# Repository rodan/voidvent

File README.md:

## voidvent

 ////// UNDER DEVELOPMENT ///////////////////////

 room climate control project that replaces the microcontroller inside a blueair pro air purifier with a transceiver-enabled cc430f5137 devboard from Olimex.

```
 source:       https://github.com/rodan/voidvent
 author:       Petre Rodan <2b4eda@subdimension.ro>
 license:      BSD
```

### Features

 * RF-based remote control of the air purifier via Intertechno ITLS-16
 * limit the ionizer activity to a custom number of minutes per hour (3 levels)
 * control air extractor via RF signal
 * control window opening via RF signal
 
### Components

project directory structure

 * ./firmware/base_station/ - source code for the base station
 * ./firmware/window_control/ - source code for the window opening jig
 * ./hardware/blueair_pro_m/ - kicad schematics of the digital subsystem of the air purifier

### Build requirements

you will need TI's excelent [GCC toolchain](https://www.ti.com/tool/MSP430-GCC-OPENSOURCE) or Code Composer Studio for linux and my [reference libraries for msp430 micros](https://github.com/rodan/atlas430) cloned in /opt/.

```
cd ./firmware/base_station
make
make install
```

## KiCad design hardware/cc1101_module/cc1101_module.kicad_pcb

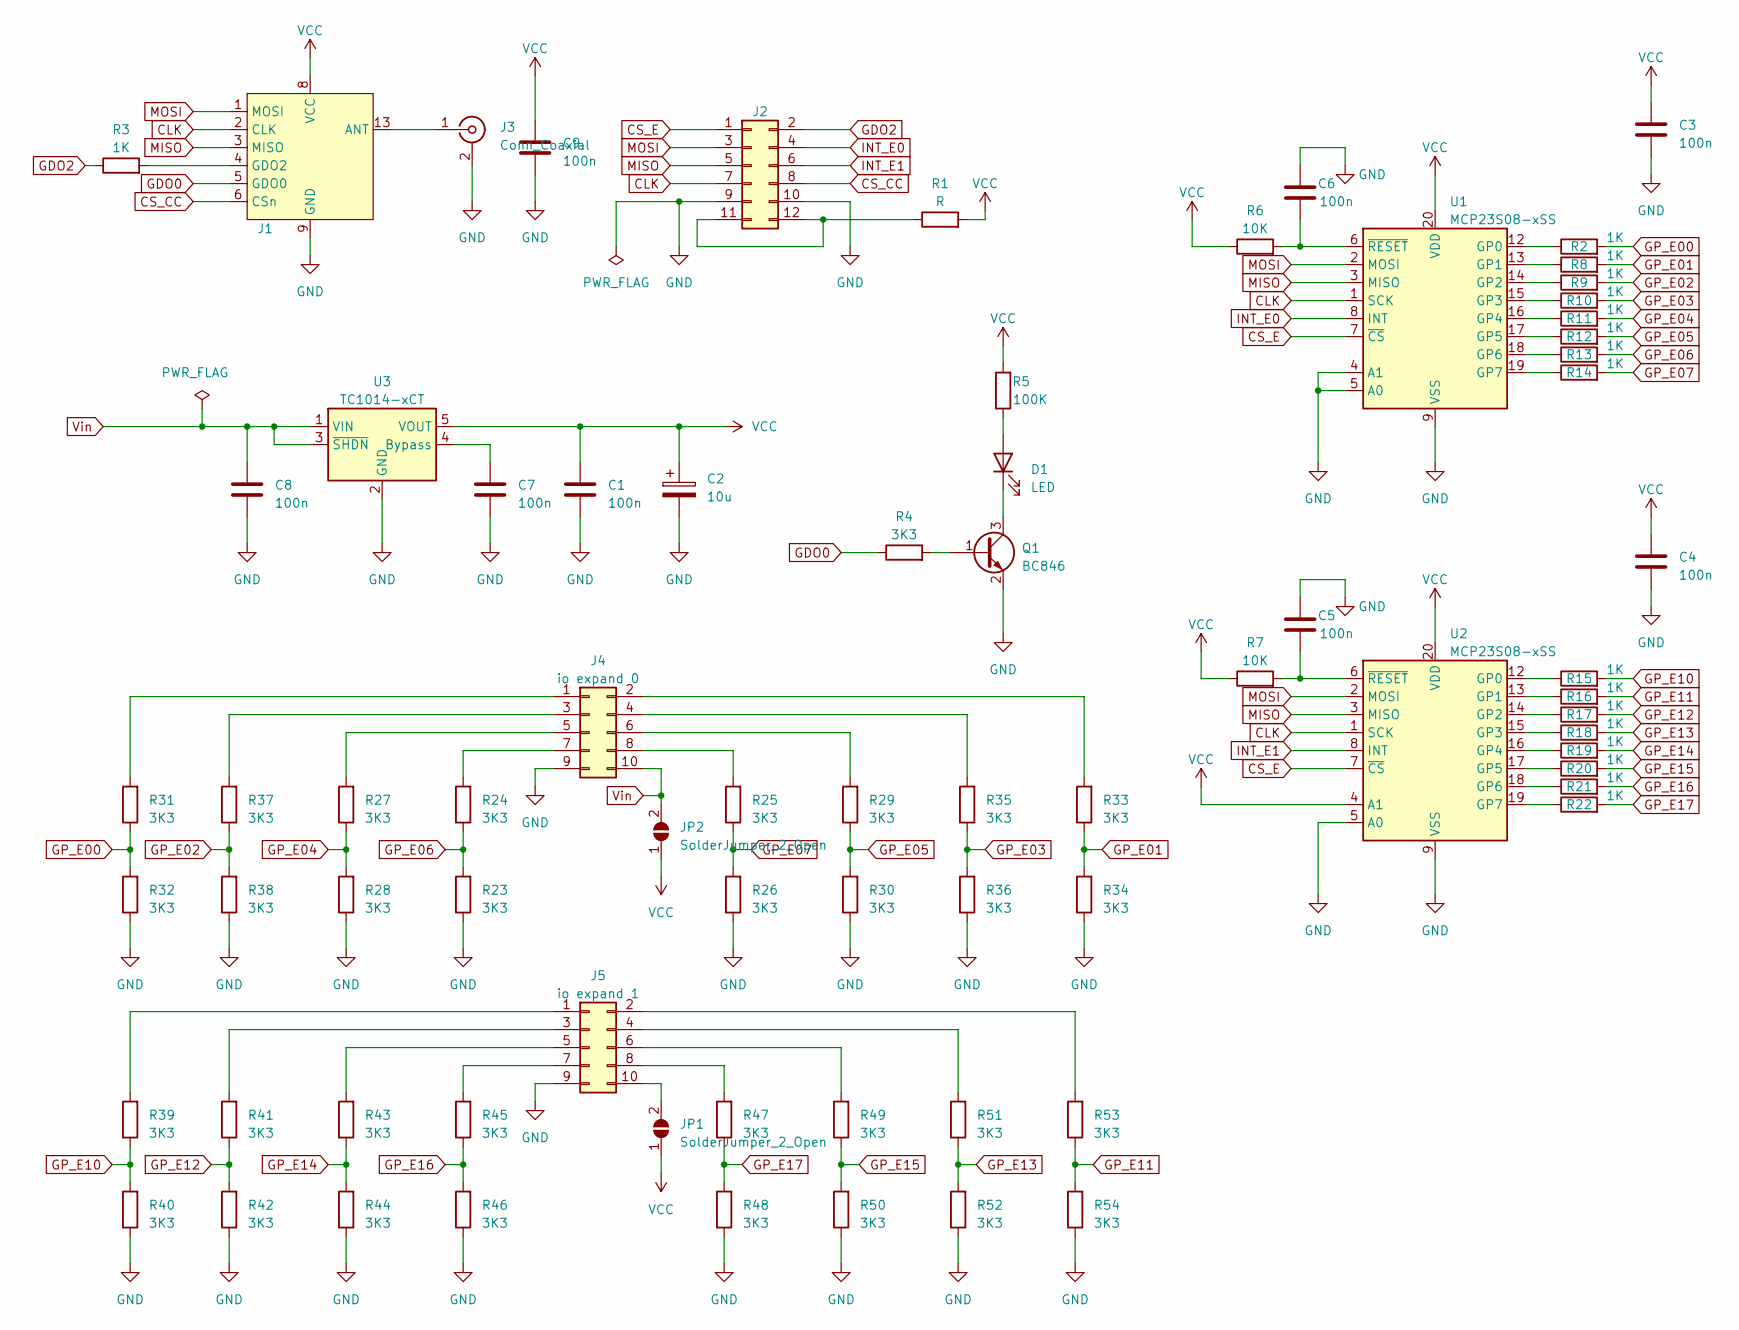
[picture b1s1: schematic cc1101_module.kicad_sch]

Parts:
C1, C3, C4, C5, C6, C7, C8, C9: 100n; C_0805_2012Metric_Pad1.18x1.45mm_HandSolder
C2: 10u; C_Elec_4x5.8
D1: LED; LED_0805_2012Metric_Pad1.15x1.40mm_HandSolder
J1: RC-CC1101-SPI-SMT
J2: Conn_02x06_Odd_Even; PinHeader_2x06_P2.54mm_Horizontal
J3: Conn_Coaxial; SMA-16
J4: io expand 0; PinHeader_2x05_P2.54mm_Horizontal
J5: io expand 1; PinHeader_2x05_P2.54mm_Horizontal
JP1, JP2: SolderJumper_2_Open; SolderJumper-2_P1.3mm_Open_TrianglePad1.0x1.5mm
Q1: BC846; SOT-23
R1: R; R_0805_2012Metric_Pad1.20x1.40mm_HandSolder
R2, R3, R8, R9, R10, R11, R12, R13, R14, R15, R16, R17, R18, R19, R20, R21, R22: 1K; R_0805_2012Metric_Pad1.20x1.40mm_HandSolder
R4, R23, R24, R25, R26, R27, R28, R29, R30, R31, R32, R33, R34, R35, R36, R37, R38, R39, R40, R41, R42, R43, R44, R45, R46, R47, R48, R49, R50, R51, R52, R53, R54: 3K3; R_0805_2012Metric_Pad1.20x1.40mm_HandSolder
R5: 100K; R_0805_2012Metric_Pad1.20x1.40mm_HandSolder
R6, R7: 10K; R_0805_2012Metric_Pad1.20x1.40mm_HandSolder
U1, U2: MCP23S08-xSS; SSOP-20_5.3x7.2mm_P0.65mm
U3: TC1014-xCT; SOT-23-5

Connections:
CLK: J1.2 (CLK), J2.7, U1.1 (SCK), U2.1 (SCK)
CS_CC: J1.6 (CSn), J2.8
CS_E: J2.1, U1.7 (~CS), U2.7 (~CS)
GDO0: J1.5 (GDO0), R4.1
GDO2: J2.2, R3.1
GND: C1.2, C2.2, C3.2, C4.2, C5.1, C6.1, C7.2, C8.2, C9.2, J1.9 (GND), J1.10 (GND), J2.9, J2.10, J3.2 (Ext), J4.9, J5.9, Q1.2 (E), R23.1, R26.1, R28.1, R30.1, R32.1, R34.1, R36.1, R38.1, R40.1, R42.1, R44.1, R46.1, R48.1, R50.1, R52.1, R54.1, U1.4 (A1), U1.5 (A0), U1.9 (VSS), U2.5 (A0), U2.9 (VSS), U3.2 (GND)
GP_E00: R2.2, R31.1, R32.2
GP_E01: R8.2, R33.1, R34.2
GP_E02: R9.2, R37.1, R38.2
GP_E03: R10.2, R35.1, R36.2
GP_E04: R11.2, R27.1, R28.2
GP_E05: R12.2, R29.1, R30.2
GP_E06: R13.2, R23.2, R24.1
GP_E07: R14.2, R25.1, R26.2
GP_E10: R15.2, R39.1, R40.2
GP_E11: R16.2, R53.1, R54.2
GP_E12: R17.2, R41.1, R42.2
GP_E13: R18.2, R51.1, R52.2
GP_E14: R19.2, R43.1, R44.2
GP_E15: R20.2, R49.1, R50.2
GP_E16: R21.2, R45.1, R46.2
GP_E17: R22.2, R47.1, R48.2
INT_E0: J2.4, U1.8 (INT)
INT_E1: J2.6, U2.8 (INT)
MISO: J1.3 (MISO), J2.5, U1.3 (MISO), U2.3 (MISO)
MOSI: J1.1 (MOSI), J2.3, U1.2 (MOSI), U2.2 (MOSI)
unnamed: D1.2 (A), R5.1
unnamed: D1.1 (K), Q1.3 (C)
unnamed: J1.13 (ANT), J3.1 (In)
unnamed: J1.4 (GDO2), R3.2
unnamed: J2.11, J2.12, R1.1
unnamed: J4.1, R31.2
unnamed: J4.2, R33.2
unnamed: J4.3, R37.2
unnamed: J4.4, R35.2
unnamed: J4.5, R27.2
unnamed: J4.6, R29.2
unnamed: J4.7, R24.2
unnamed: J4.8, R25.2
unnamed: J5.1, R39.2
unnamed: J5.2, R53.2
unnamed: J5.3, R41.2
unnamed: J5.4, R51.2
unnamed: J5.5, R43.2
unnamed: J5.6, R49.2
unnamed: J5.7, R45.2
unnamed: J5.8, R47.2
unnamed: J5.10, JP1.2 (B)
unnamed: Q1.1 (B), R4.2
unnamed: R2.1, U1.12 (GP0)
unnamed: R8.1, U1.13 (GP1)
unnamed: R9.1, U1.14 (GP2)
unnamed: R10.1, U1.15 (GP3)
unnamed: R11.1, U1.16 (GP4)
unnamed: R12.1, U1.17 (GP5)
unnamed: R13.1, U1.18 (GP6)
unnamed: R14.1, U1.19 (GP7)
unnamed: C6.2, R6.2, U1.6 (~RESET)
unnamed: R15.1, U2.12 (GP0)
unnamed: R16.1, U2.13 (GP1)
unnamed: R17.1, U2.14 (GP2)
unnamed: R18.1, U2.15 (GP3)
unnamed: R19.1, U2.16 (GP4)
unnamed: R20.1, U2.17 (GP5)
unnamed: R21.1, U2.18 (GP6)
unnamed: R22.1, U2.19 (GP7)
unnamed: C5.2, R7.2, U2.6 (~RESET)
unnamed: C7.1, U3.4 (Bypass)
VCC: C1.1, C2.1, C3.1, C4.1, C9.1, J1.7 (VCC), J1.8 (VCC), JP1.1 (A), JP2.1 (A), R1.2, R5.2, R6.1, R7.1, U1.20 (VDD), U2.4 (A1), U2.20 (VDD), U3.5 (VOUT)
Vin: C8.1, J4.10, JP2.2 (B), U3.1 (VIN), U3.3 (~SHDN)

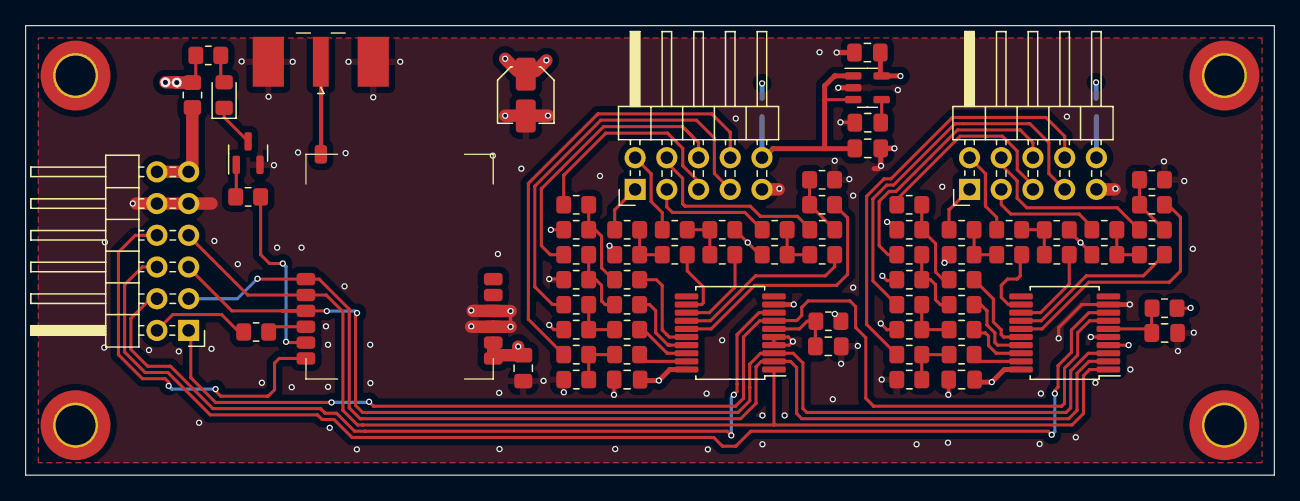
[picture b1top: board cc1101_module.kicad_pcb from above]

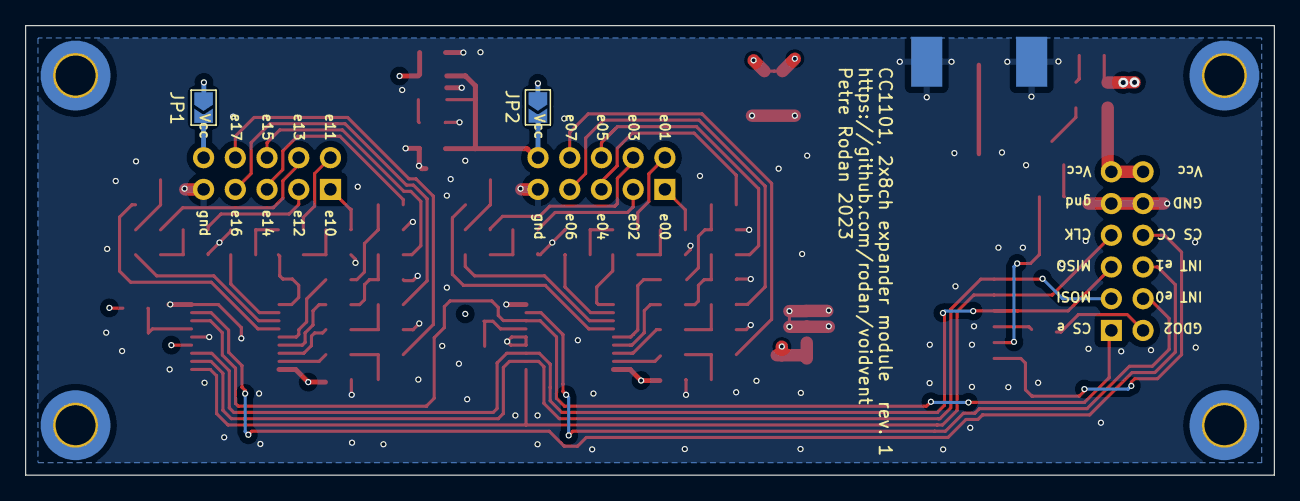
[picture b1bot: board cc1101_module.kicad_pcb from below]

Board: 4 copper layers, 100.0 x 36.0 mm, 75 parts (2 on the bottom side), 70 nets.

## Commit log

2022-12-25 add license
2023-01-06 capture signals generated by the itls16 remote
2023-01-07 add skeleton fw
2023-01-08 TX for first intertechno protocol is working
2023-01-09 cleanup
2023-01-09 add CCS project structure
2023-01-10 generate rf calibration settings with SmartRF Studio
2023-01-10 TX cleanup
2023-01-10 RX handler implemented
2023-01-11 decode of the variable Intertechno protocol
2023-01-17 add modulated freq to doc
2023-01-17 expand rf struct
2023-01-19 implement rf testing logic
2023-01-19 rx/tx test working
2023-01-20 print buffer after rx
2023-01-21 detect it_fixed signal above threshold via RFIFG13
2023-01-22 add POR cmd, fix lack of RX upon POR
2023-01-22 add scheduler based on timer1a
2023-01-23 irq handler for the async demodulated signal present on GDO1
2023-01-23 variable length intertechno RX decode success
2023-01-25 add fixed proto decoding, add vote for protocol detection
2023-01-26 tweak protocol voting
2023-01-26 add power management skel
2023-01-27 power management working: 200ms sleep, 10ms RX
2023-01-29 the variable protocol is a manchester encoded, timing-defined low bit signal - rewrite the decoder to treat it as such
2023-01-29 protocol decode rewrite
2023-01-29 add manchester reference
2023-02-01 use updated scheduler functions from atlas430
2023-02-01 add hamma weather station decoder part1
2023-02-02 hamma weather station decoder part2
2023-02-02 fix typo in product name
2023-02-02 hama weater station protocol decoded
2023-08-25 add cc1101 module pcb
2023-08-26 repo rename
2023-08-28 pcb update
2023-08-31 add pins
2023-09-13 pcb verified
2023-09-20 pcb sent to production
